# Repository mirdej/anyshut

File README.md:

# THE   [ a n y m a ]   SHUTTER

Versatile, modular ,3D-printed, remote controlled shutter for video beamers and other light sources.
 
- Can be mounted to the projector in various ways
- Opens to the front or to the side
- Test button on the device
- Wireless remote control through ESP-Now over ~25m
- DMX input to the remote, no need to install cables

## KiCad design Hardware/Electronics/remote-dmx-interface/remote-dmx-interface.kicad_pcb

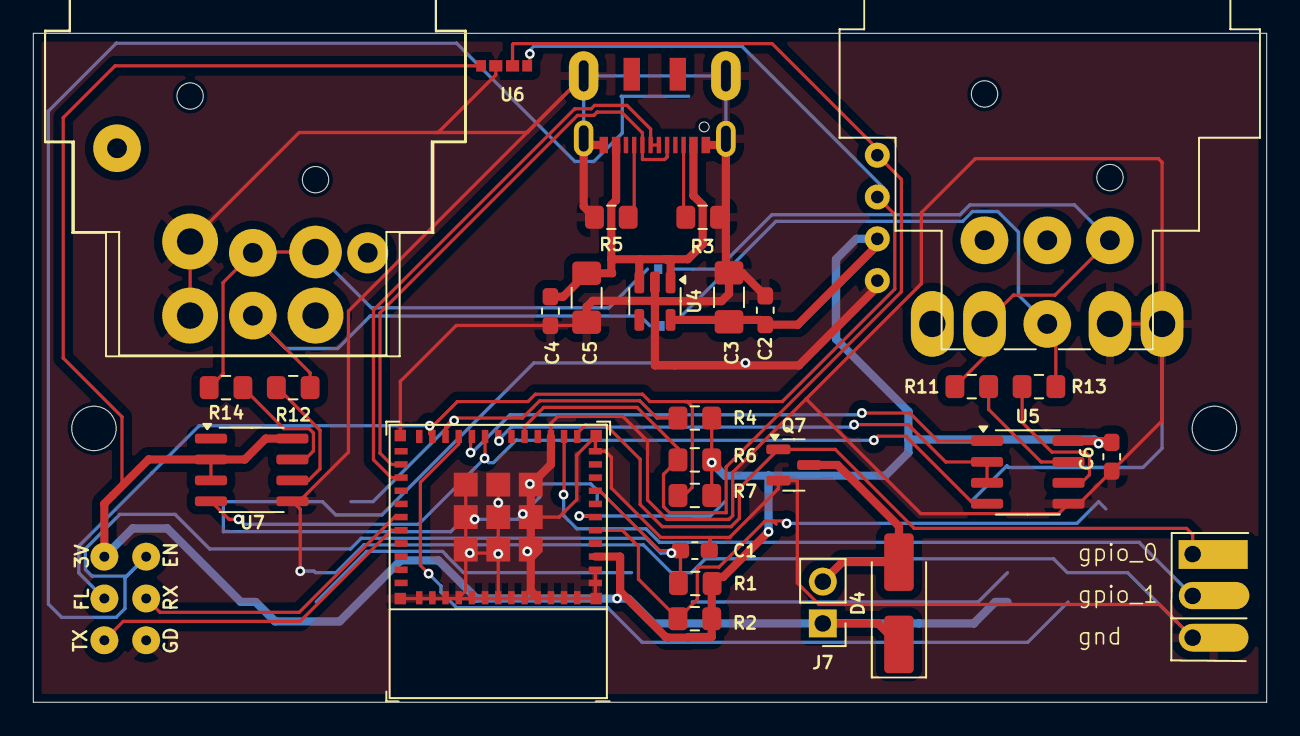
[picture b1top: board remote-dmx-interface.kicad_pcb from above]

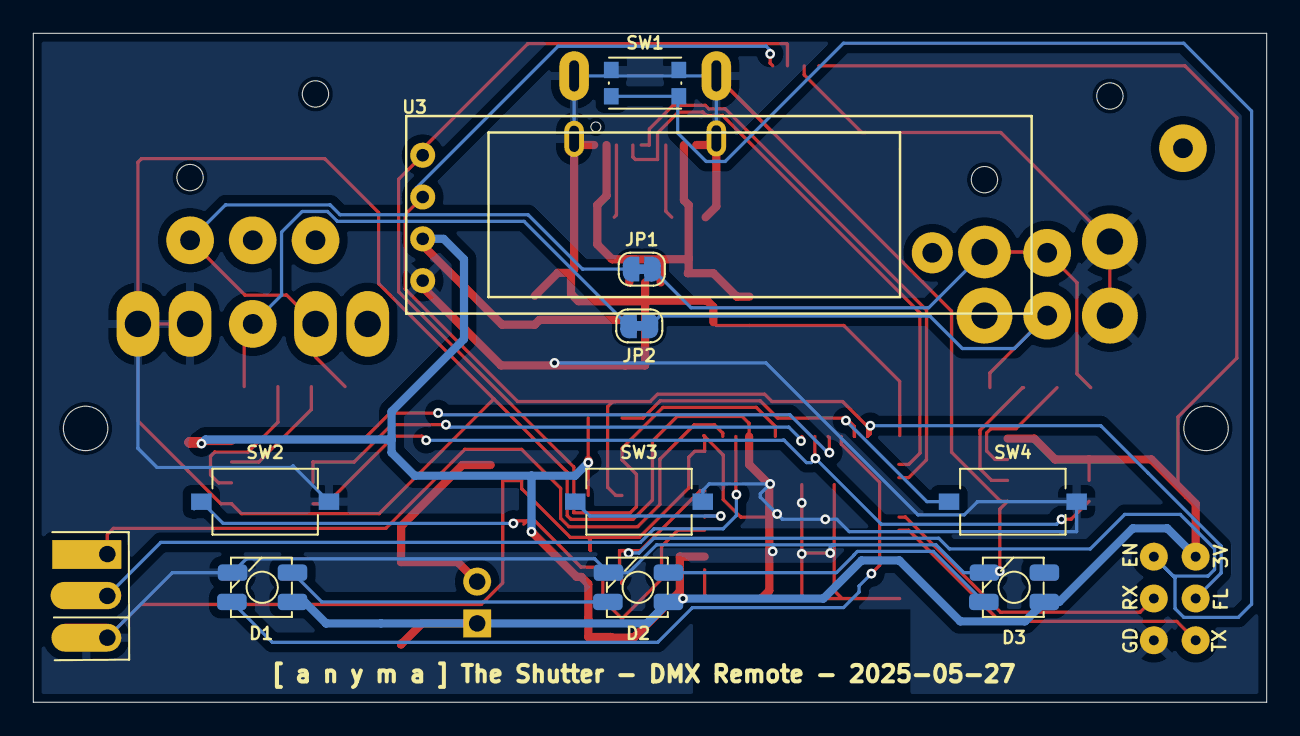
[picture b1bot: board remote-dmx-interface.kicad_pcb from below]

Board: 2 copper layers, 74.9 x 40.6 mm, 42 parts (11 on the bottom side), 32 nets.

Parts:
C1: 1u; C_0603_1608Metric_Pad1.05x0.95mm_HandSolder
C2, C4, C6: 100n; C_0603_1608Metric_Pad1.05x0.95mm_HandSolder
C3, C5: 10u; C_1206_3216Metric_Pad1.42x1.75mm_HandSolder
D1, D2, D3: SK6812MINI; SK6812-MINI-HS
D4: 1N4148WT; D_SMA_Handsoldering
H2, H5: MountingHole; MountingHole_2.7mm_M2.5_DIN965
J2: Prog; ESP-POGO-PROG-THT
J3: USB_C_Receptacle_USB2.0; JAE_USB-C_SJ122205
J4: DMX-OUT; Jack_XLR_Neutrik_3+5Pin_Female
J5: spare; ComboPinhead_03
J6: DMX-IN; Jack_XLR_Neutrix__3+5Pin_Male
J7: Vibro; PinHeader_1x02_P2.54mm_Vertical
JP1: Cut for MERGER Mode; SolderJumper-2_P1.3mm_Bridged_RoundedPad1.0x1.5mm
JP2: Cut for MERGER mode; SolderJumper-2_P1.3mm_Bridged_RoundedPad1.0x1.5mm
Q7: IRLML0030TRPBF; SOT-23
R1, R2, R3, R4, R5, R6, R7: 5k1; R_0805_2012Metric_Pad1.15x1.40mm_HandSolder
R11, R13: 22; R_0805_2012Metric_Pad1.15x1.40mm_HandSolder
R12, R14: (22); R_0805_2012Metric_Pad1.15x1.40mm_HandSolder
SW1: Reset; SW_Push_1P1T_NO_CK_KMR2
SW2: Btn-1; SW_Tactile_SPST_NO_Straight_CK_PTS636Sx25SMTRLFS
SW3: Btn-2; SW_Tactile_SPST_NO_Straight_CK_PTS636Sx25SMTRLFS
SW4: Btn-3; SW_Tactile_SPST_NO_Straight_CK_PTS636Sx25SMTRLFS
U1: ESP32-C3-MINI-1
U3: i2c-display128x32; Bangood-OLED-128x32
U4: XC6220B331MR; SOT-23-5
U5: SP3485EN; SOIC-8_3.9x4.9mm_P1.27mm
U6: VEML3328; VEML3328SL
U7: (SP3485EN) for MERGER Mode; SOIC-8_3.9x4.9mm_P1.27mm

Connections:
+3V3: C2.1, C3.1, C6.1, D1.4 (VDD), D2.4 (VDD), D3.4 (VDD), D4.1 (K), J2.1, J7.1, R1.1, R2.1, R4.1, R6.1, R7.1, U1.3 (3V3), U3.2 (VCC), U4.5 (VOUT), U5.8 (VCC), U6.1 (VCC), U7.2 (~RE), U7.3 (DE), U7.8 (VCC)
+5V: C4.1, C5.1, J3.A4 (VBUS), J3.A9 (VBUS), U4.1 (VIN), U4.3 (CE)
/DMX_DIR: U1.18 (GPIO4/ADC1_CH4), U5.2 (~RE), U5.3 (DE)
/DMX_RX: U1.20 (GPIO6), U5.1 (RO)
/DMX_TX: U1.19 (GPIO5/ADC2_CH0), U5.4 (DI), U7.4 (DI)
/en: C1.1, J2.2, R1.2, SW1.2, U1.8 (EN/CHIP_PU)
/flash: J2.3, R7.2, U1.23 (GPIO9), U3.3 (SCL), U6.4 (SCL)
/gpio_0: J5.1, Q7.1 (G), U1.12 (GPIO0/ADC1_CH0/XTAL_32K_P)
/gpio_1: J5.2, U1.13 (GPIO1/ADC1_CH1/XTAL_32K_N)
/pix: D1.3 (DIN), U1.21 (GPIO7)
/rx: J2.4, U1.30 (GPIO20/U0RXD)
/sda: R6.2, U1.16 (GPIO10), U3.4 (SDA), U6.3 (SDA)
/strap1: R4.2, SW4.1, U1.22 (GPIO8)
/strap2: R2.2, SW2.1, U1.5 (GPIO2/ADC1_CH2)
/tx: J2.5, U1.31 (GPIO21/U0TXD)
/usb+: J3.A6 (D+), J3.B6 (D+), U1.27 (GPIO19/USB_D+)
/usb-: J3.A7 (D-), J3.B7 (D-), U1.26 (GPIO18/USB_D-)
GND: C1.2, C2.2, C3.2, C4.2, C5.2, C6.2, D1.2 (VSS), D2.2 (VSS), D3.2 (VSS), J2.6, J3.A1 (GND), J3.A12 (GND), J3.S1 (SHIELD), J4.1, J5.3, J6.1, Q7.2 (S), R3.2, R5.2, SW1.1, SW2.2, SW3.2, SW4.2, U1.1 (GND), U1.2 (GND), U1.11 (GND), U1.14 (GND), U1.36 (GND), U1.37 (GND), U1.38 (GND), U1.39 (GND), U1.40 (GND), U1.41 (GND), U1.42 (GND), U1.43 (GND), U1.44 (GND), U1.45 (GND), U1.46 (GND), U1.47 (GND), U1.48 (GND), U1.49 (GND), U1.50 (GND), U1.51 (GND), U1.52 (GND), U1.53 (GND), U3.1 (GND), U4.2 (GND), U5.5 (GND), U6.2 (GND), U7.5 (GND)
unnamed: D1.1 (DOUT), D2.3 (DIN)
unnamed: D2.1 (DOUT), D3.3 (DIN)
unnamed: D4.2 (A), J7.2, Q7.3 (D)
unnamed: J3.A5 (CC1), R3.1
unnamed: J3.B5 (CC2), R5.1
unnamed: J6.2, JP1.1 (A), R11.1
unnamed: J4.2, JP1.2 (B), R14.1
unnamed: J6.3, JP2.1 (A), R13.1
unnamed: J4.3, JP2.2 (B), R12.1
unnamed: SW3.1, U1.6 (GPIO3/ADC1_CH3)
unnamed: R13.2, U5.6 (A)
unnamed: R11.2, U5.7 (B)
unnamed: R12.2, U7.6 (A)
unnamed: R14.2, U7.7 (B)

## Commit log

2024-07-19 initaial commit
2024-07-19 softap+espnow
2024-08-03 cleanup 3d, readme
2025-06-04 remote dmx - new hardware, old firmware
2025-06-23 switch to Agora
2025-06-23 add dmx
